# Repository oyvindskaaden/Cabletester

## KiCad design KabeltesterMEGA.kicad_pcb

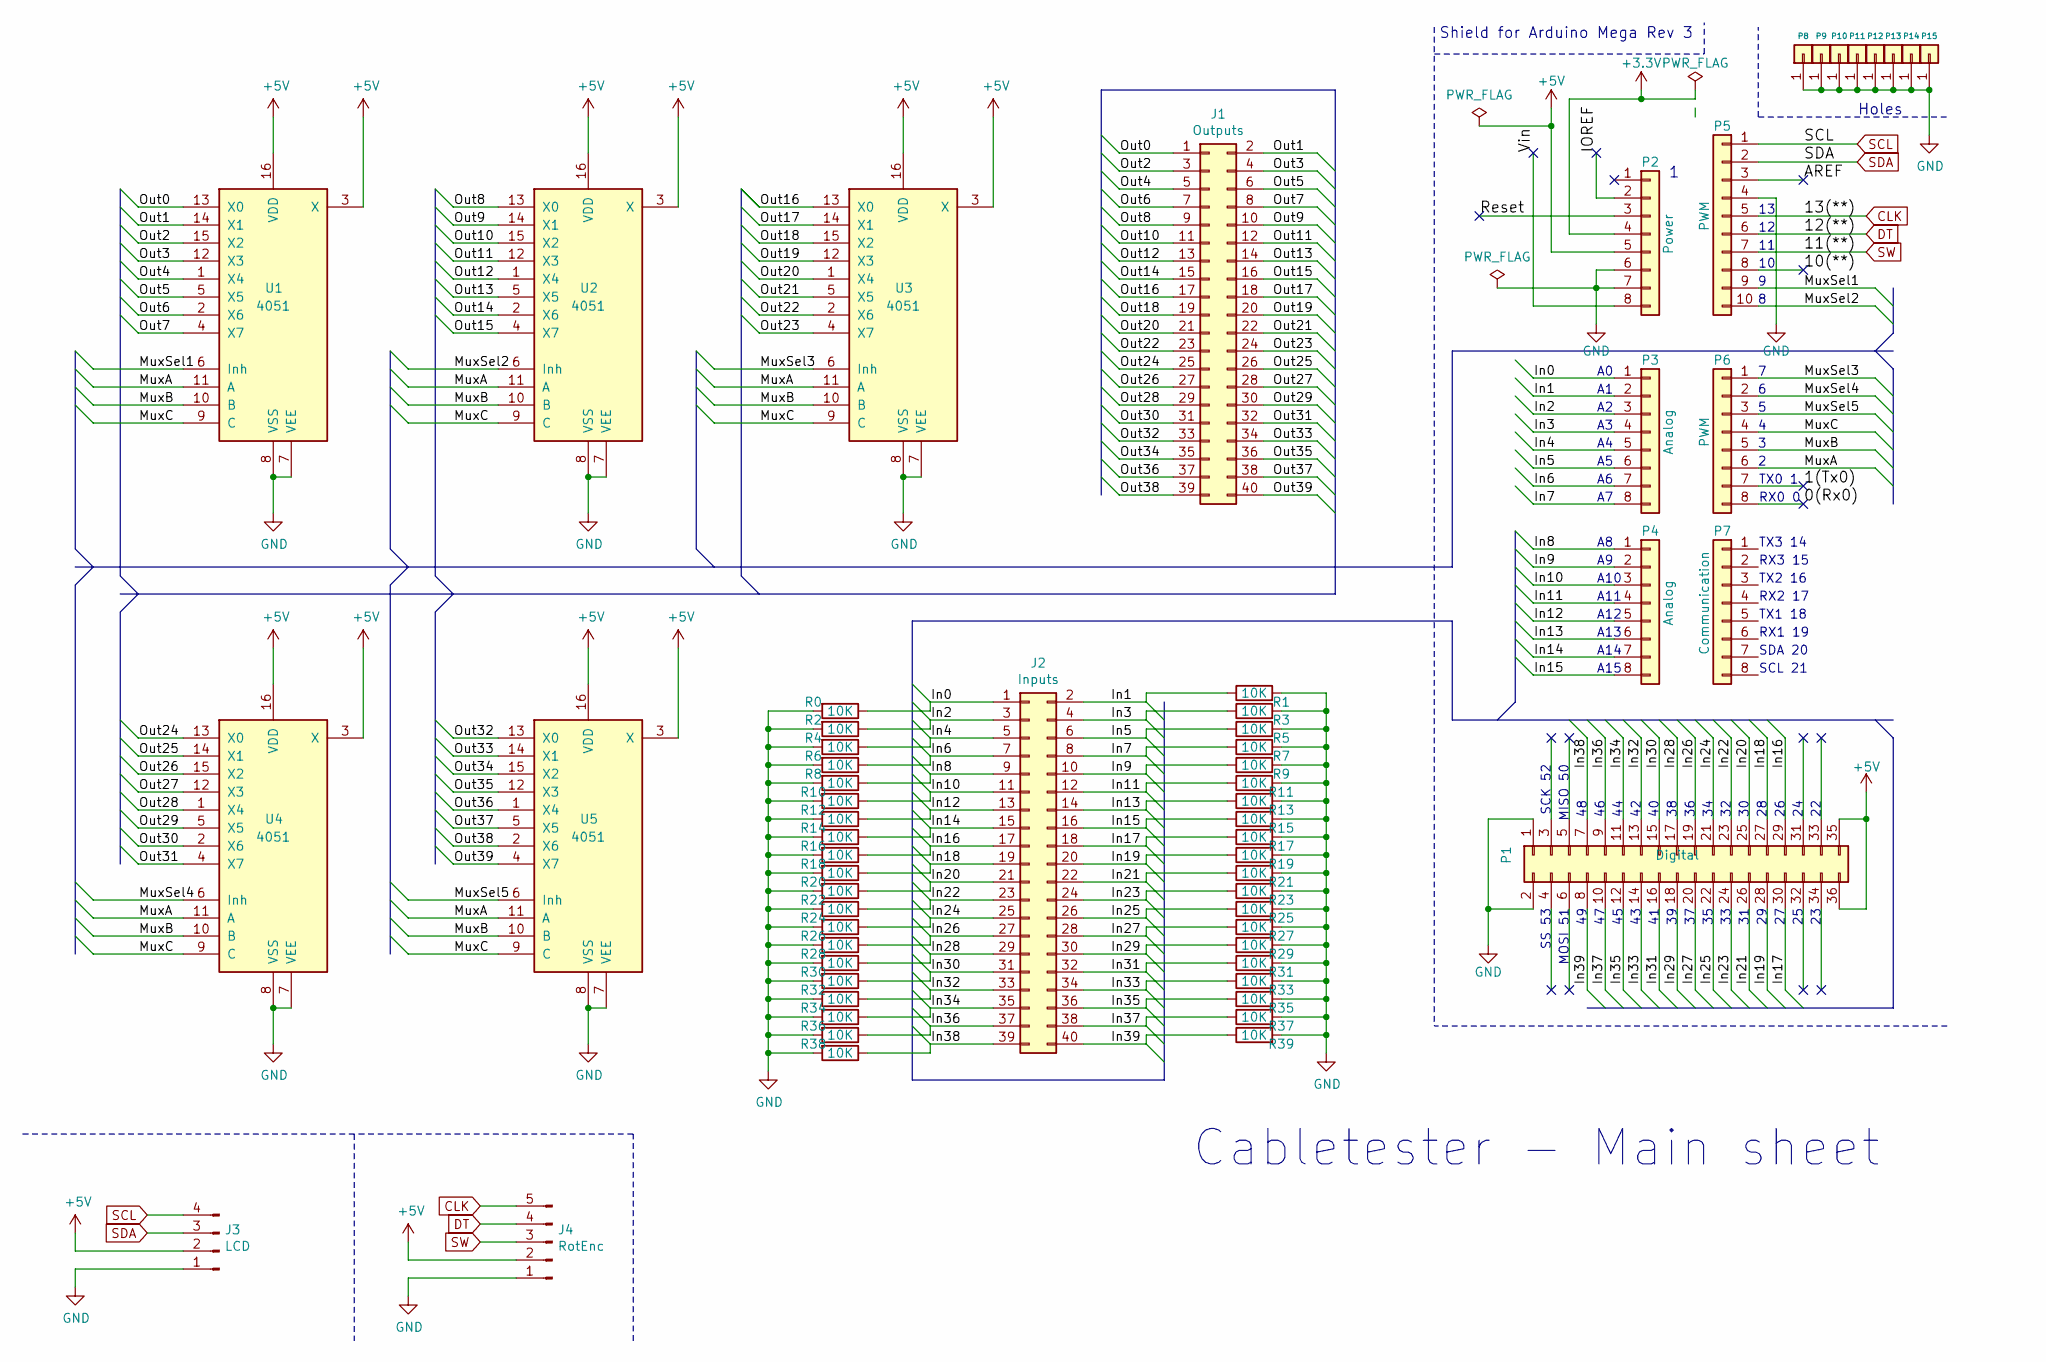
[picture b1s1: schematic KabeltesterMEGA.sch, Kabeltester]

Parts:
J1: Outputs; IDC-Header_2x20_P2.54mm_Vertical
J2: Inputs; IDC-Header_2x20_P2.54mm_Vertical
J3: LCD; PinHeader_1x04_P2.54mm_Vertical
J4: RotEnc; PinHeader_1x05_P2.54mm_Vertical
P1: Digital; Socket_Strip_Arduino_2x18
P2: Power; Socket_Strip_Arduino_1x08
P3, P4: Analog; Socket_Strip_Arduino_1x08
P5: PWM; Socket_Strip_Arduino_1x10
P6: PWM; Socket_Strip_Arduino_1x08
P7: Communication; Socket_Strip_Arduino_1x08
P8, P9, P10, P11, P12, P13, P14, P15: CONN_01X01; Arduino_1pin
R0, R1, R2, R3, R4, R5, R6, R7, R8, R9, R10, R11, R12, R13, R14, R15, R16, R17, R18, R19, R20, R21, R22, R23, R24, R25, R26, R27, R28, R29, R30, R31, R32, R33, R34, R35, R36, R37, R38, R39: 10K; R_0603_1608Metric_Pad1.05x0.95mm_HandSolder
U1, U2, U3, U4, U5: 4051; DIP-16_W7.62mm_LongPads

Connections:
+3V3: P2.4
+5V: J3.2, J4.2, P1.35, P1.36, P2.5, U1.3 (X), U1.16 (VDD), U2.3 (X), U2.16 (VDD), U3.3 (X), U3.16 (VDD), U4.3 (X), U4.16 (VDD), U5.3 (X), U5.16 (VDD)
/0(Rx0): P6.8
/1(Tx0): P6.7
/10(**): P5.8
/AREF: P5.3
/IOREF: P2.2
/In0: J2.1, P3.1, R0.1
/In1: J2.2, P3.2, R1.1
/In2: J2.3, P3.3, R2.1
/In3: J2.4, P3.4, R3.1
/In4: J2.5, P3.5, R4.1
/In5: J2.6, P3.6, R5.1
/In6: J2.7, P3.7, R6.1
/In7: J2.8, P3.8, R7.1
/In8: J2.9, P4.1, R8.1
/In9: J2.10, P4.2, R9.1
/In10: J2.11, P4.3, R10.1
/In11: J2.12, P4.4, R11.1
/In12: J2.13, P4.5, R12.1
/In13: J2.14, P4.6, R13.1
/In14: J2.15, P4.7, R14.1
/In15: J2.16, P4.8, R15.1
/In16: J2.17, P1.29, R16.1
/In17: J2.18, P1.30, R17.1
/In18: J2.19, P1.27, R18.1
/In19: J2.20, P1.28, R19.1
/In20: J2.21, P1.25, R20.1
/In21: J2.22, P1.26, R21.1
/In22: J2.23, P1.23, R22.1
/In23: J2.24, P1.24, R23.1
/In24: J2.25, P1.21, R24.1
/In25: J2.26, P1.22, R25.1
/In26: J2.27, P1.19, R26.1
/In27: J2.28, P1.20, R27.1
/In28: J2.29, P1.17, R28.1
/In29: J2.30, P1.18, R29.1
/In30: J2.31, P1.15, R30.1
/In31: J2.32, P1.16, R31.1
/In32: J2.33, P1.13, R32.1
/In33: J2.34, P1.14, R33.1
/In34: J2.35, P1.11, R34.1
/In35: J2.36, P1.12, R35.1
/In36: J2.37, P1.9, R36.1
/In37: J2.38, P1.10, R37.1
/In38: J2.39, P1.7, R38.1
/In39: J2.40, P1.8, R39.1
/MuxA: P6.6, U1.11 (A), U2.11 (A), U3.11 (A), U4.11 (A), U5.11 (A)
/MuxB: P6.5, U1.10 (B), U2.10 (B), U3.10 (B), U4.10 (B), U5.10 (B)
/MuxC: P6.4, U1.9 (C), U2.9 (C), U3.9 (C), U4.9 (C), U5.9 (C)
/MuxSel1: P5.9, U1.6 (Inh)
/MuxSel2: P5.10, U2.6 (Inh)
/MuxSel3: P6.1, U3.6 (Inh)
/MuxSel4: P6.2, U4.6 (Inh)
/MuxSel5: P6.3, U5.6 (Inh)
/Out0: J1.1, U1.13 (X0)
/Out1: J1.2, U1.14 (X1)
/Out2: J1.3, U1.15 (X2)
/Out3: J1.4, U1.12 (X3)
/Out4: J1.5, U1.1 (X4)
/Out5: J1.6, U1.5 (X5)
/Out6: J1.7, U1.2 (X6)
/Out7: J1.8, U1.4 (X7)
/Out8: J1.9, U2.13 (X0)
/Out9: J1.10, U2.14 (X1)
/Out10: J1.11, U2.15 (X2)
/Out11: J1.12, U2.12 (X3)
/Out12: J1.13, U2.1 (X4)
/Out13: J1.14, U2.5 (X5)
/Out14: J1.15, U2.2 (X6)
/Out15: J1.16, U2.4 (X7)
/Out16: J1.17, U3.13 (X0)
/Out17: J1.18, U3.14 (X1)
/Out18: J1.19, U3.15 (X2)
/Out19: J1.20, U3.12 (X3)
/Out20: J1.21, U3.1 (X4)
/Out21: J1.22, U3.5 (X5)
/Out22: J1.23, U3.2 (X6)
/Out23: J1.24, U3.4 (X7)
/Out24: J1.25, U4.13 (X0)
/Out25: J1.26, U4.14 (X1)
/Out26: J1.27, U4.15 (X2)
/Out27: J1.28, U4.12 (X3)
/Out28: J1.29, U4.1 (X4)
/Out29: J1.30, U4.5 (X5)
/Out30: J1.31, U4.2 (X6)
/Out31: J1.32, U4.4 (X7)
/Out32: J1.33, U5.13 (X0)
/Out33: J1.34, U5.14 (X1)
/Out34: J1.35, U5.15 (X2)
/Out35: J1.36, U5.12 (X3)
/Out36: J1.37, U5.1 (X4)
/Out37: J1.38, U5.5 (X5)
/Out38: J1.39, U5.2 (X6)
/Out39: J1.40, U5.4 (X7)
/Reset: P2.3
/Vin: P2.8
CLK: J4.5, P5.5
DT: J4.4, P5.6
GND: J3.1, J4.1, P1.1, P1.2, P2.6, P2.7, P5.4, P8.1, P9.1, P10.1, P11.1, P12.1, P13.1, P14.1, P15.1, R0.2, R1.2, R2.2, R3.2, R4.2, R5.2, R6.2, R7.2, R8.2, R9.2, R10.2, R11.2, R12.2, R13.2, R14.2, R15.2, R16.2, R17.2, R18.2, R19.2, R20.2, R21.2, R22.2, R23.2, R24.2, R25.2, R26.2, R27.2, R28.2, R29.2, R30.2, R31.2, R32.2, R33.2, R34.2, R35.2, R36.2, R37.2, R38.2, R39.2, U1.7 (VEE), U1.8 (VSS), U2.7 (VEE), U2.8 (VSS), U3.7 (VEE), U3.8 (VSS), U4.7 (VEE), U4.8 (VSS), U5.7 (VEE), U5.8 (VSS)
SCL: J3.4, P5.1
SDA: J3.3, P5.2
SW: J4.3, P5.7

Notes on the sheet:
Shield for Arduino Mega Rev 3
Holes
Cabletester - Main sheet
TX0 1
TX3 14
RX3 15
TX2 16
RX2 17
TX1 18
RX1 19
SDA 20
SCL 21
MISO 50
MOSI 51
SCK 52
SS 53
RX0 0
A10
A11
A12
A13
A14
A15

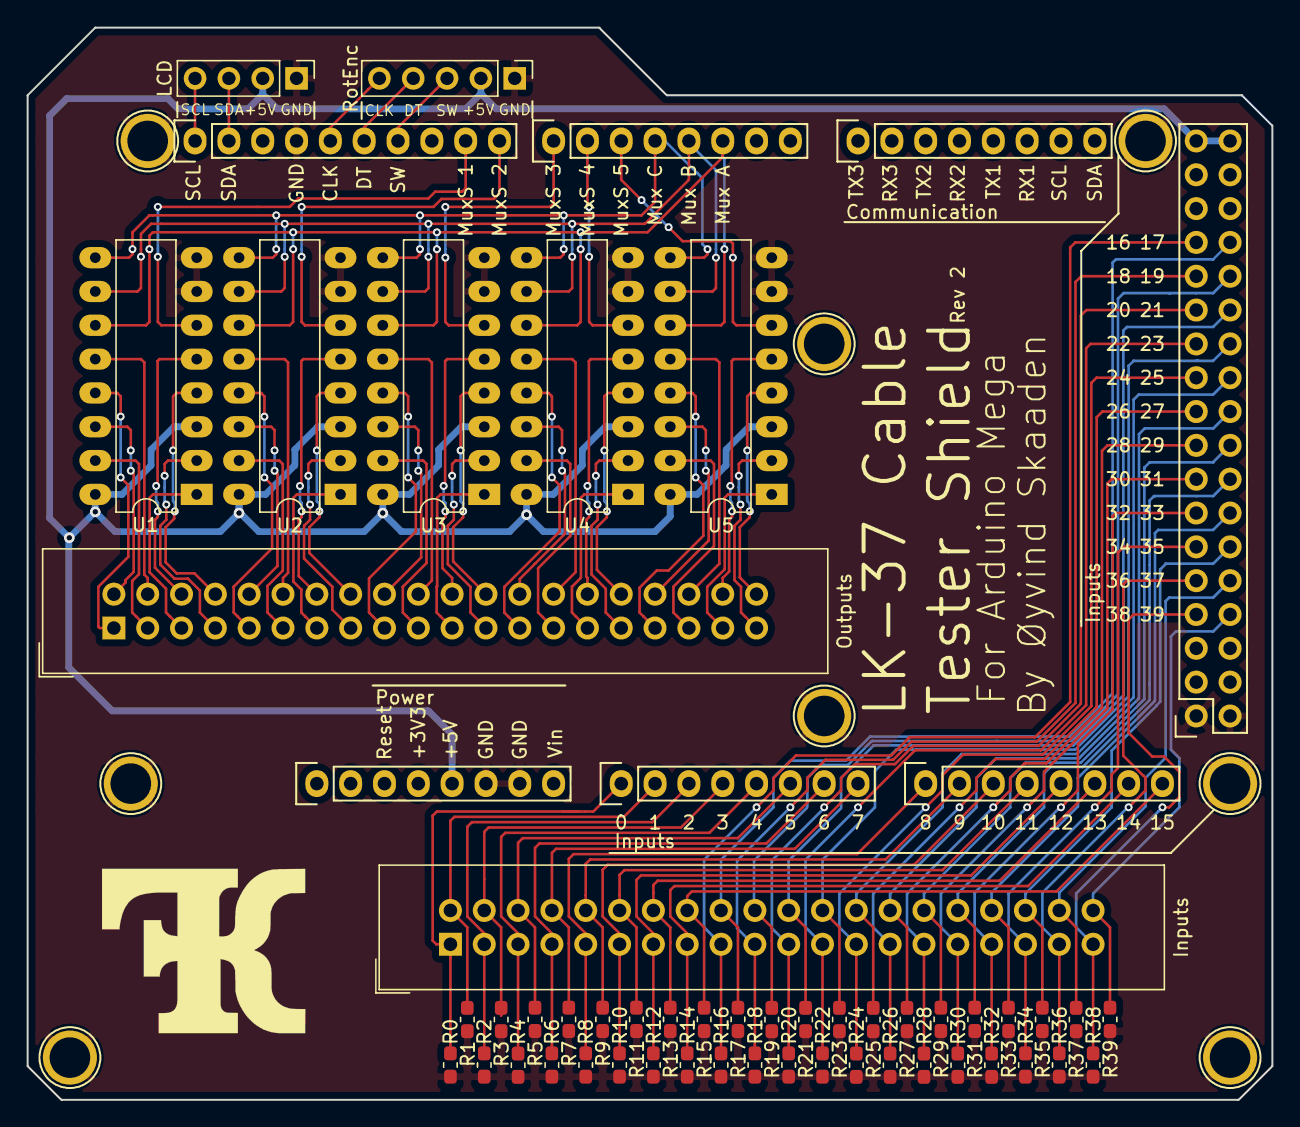
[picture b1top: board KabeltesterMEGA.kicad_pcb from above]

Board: 2 copper layers, 93.5 x 80.5 mm, 65 parts (1 on the bottom side), 95 nets.

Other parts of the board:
QR1: oyvindskaaden/Cabletester; Github-SilkNonInv

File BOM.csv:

Comment,Designator,Footprint,LCSC Part Number
10K, "R39,R38,R37,R36,R35,R34,R33,R32,R31,R30,R29,R28,R27,R26,R25,R24,R23,R22,R21,R20,R19,R18,R17,R16,R15,R14,R13,R12,R11,R10,R7,R6,R5,R4,R3,R2,R1,R0,R9,R8",0603,

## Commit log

2020-04-01 Added project
2020-04-02 Fixed typo in B-SilkS
